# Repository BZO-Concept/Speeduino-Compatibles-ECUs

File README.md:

# Speeduino-Compatibles-ECUs
everything we need for run BZO ECUs

use .ini in ECUdef file in Tunerstudio, with the good firmware. 
Firmwares are uploaded with XLoader (https://github.com/binaryupdates/xLoader) for Arduino, and STM32Cube IDE for STM32

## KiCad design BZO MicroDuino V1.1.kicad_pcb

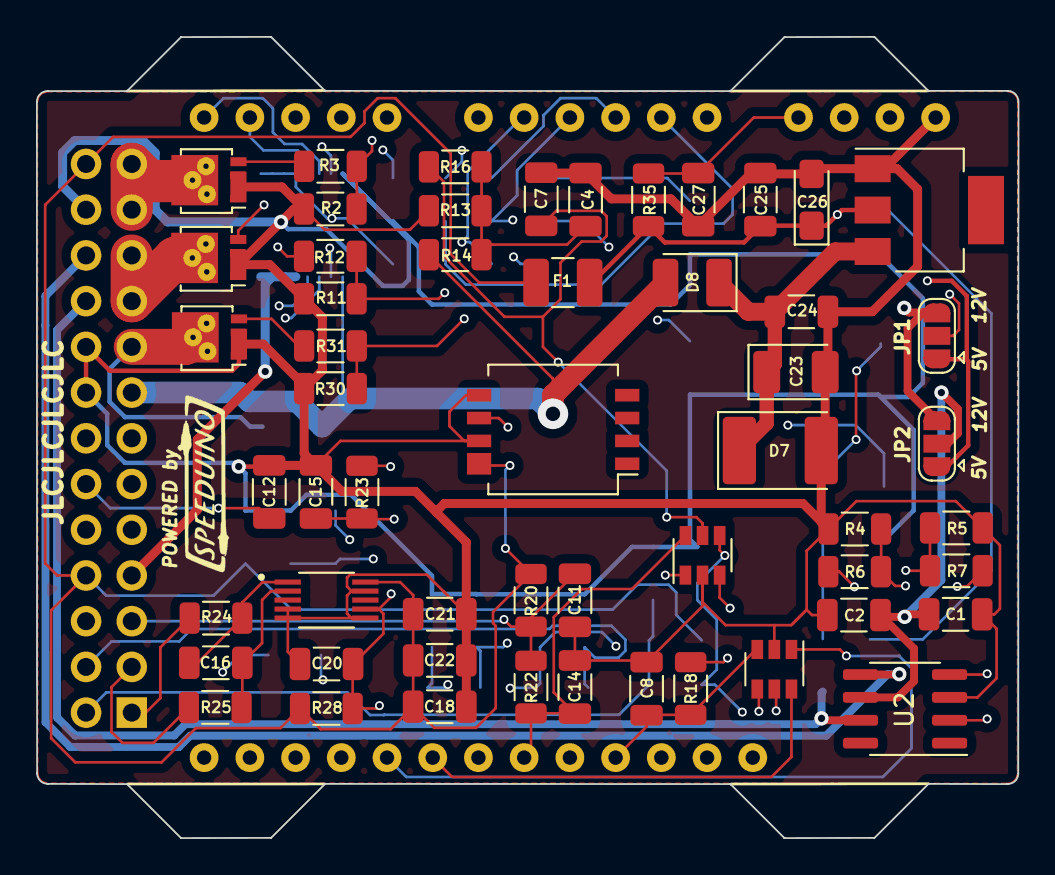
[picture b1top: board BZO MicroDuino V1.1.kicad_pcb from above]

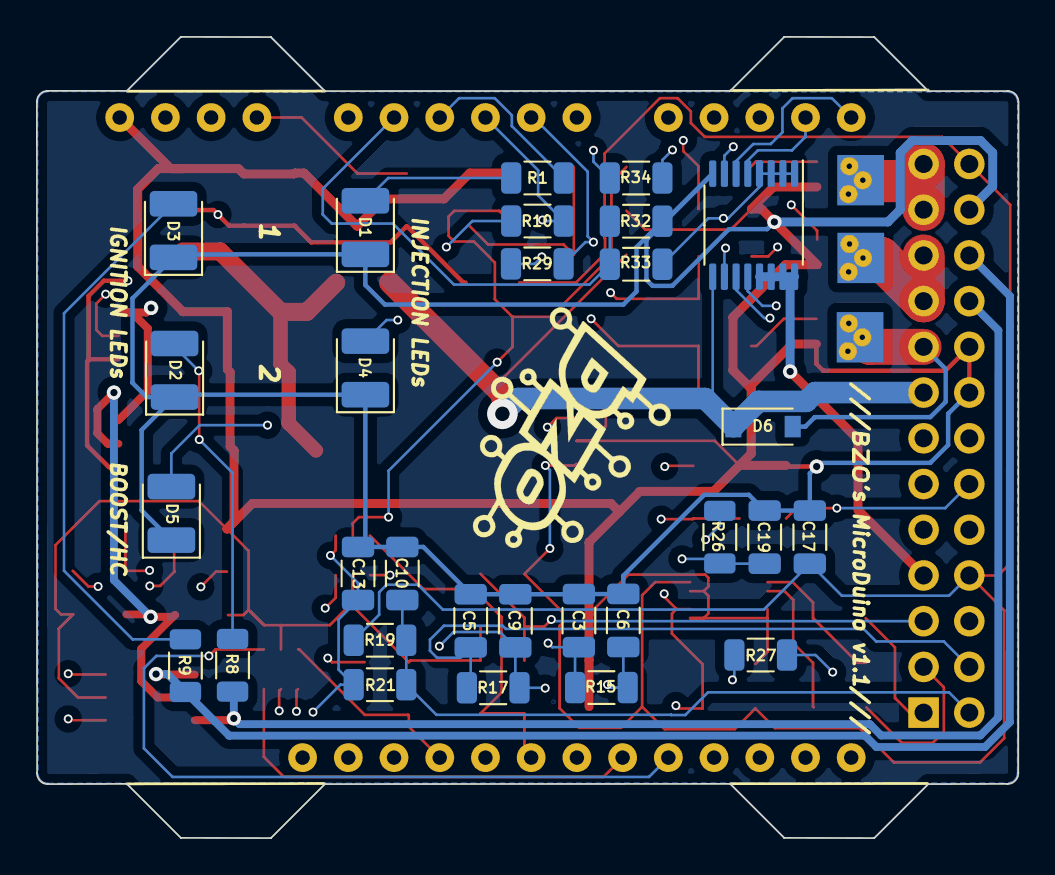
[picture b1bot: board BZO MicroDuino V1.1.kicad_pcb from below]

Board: 4 copper layers, 54.5 x 44.5 mm, 87 parts (30 on the bottom side), 60 nets.

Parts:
C1, C3, C4, C5, C10, C11, C12, C17, C19, C21, C24, C25: 0.1uF; C_1206_3216Metric
C2, C22: 1uF; C_1206_3216Metric
C6, C7, C9, C13, C14, C15: 0.22uF; C_1206_3216Metric
C8: 470pf; C_1206_3216Metric
C16: 0.001uF; C_1206_3216Metric
C18, C20: 0.01uF; C_1206_3216Metric
C23: 10uF; CP_EIA-3528-21_Kemet-B_Pad1.50x2.35mm_HandSolder
C26: 47uF; CP_EIA-3216-10_Kemet-I_Pad1.58x1.35mm_HandSolder
C27: 22uF; C_1206_3216Metric
D1, D2, D3, D4#2, D5: LED; LED_1210_3225Metric_Pad1.42x2.65mm_HandSolder
D4: LED; logo BZO
D6: 1N4448WQ-7-F; D_SOD-123
D7: D_TVS; D_2114_3652Metric_Pad1.85x3.75mm_HandSolder
D8: RB060MM-60TR; LED_1210_3225Metric_Pad1.42x2.65mm_HandSolder
F1: Polyfuse; Fuse_1210_3225Metric_Pad1.42x2.65mm_HandSolder
J1: Conn_02x13_Counter_Clockwise; PinHeader_2x13_P2.54mm_Horizontal
JP1, JP2: SolderJumper_3_Open; SolderJumper-3_P1.3mm_Open_RoundedPad1.0x1.5mm
Q1, Q2, Q3: Q_NMOS_GDS; LFPAK33_POWERPAD
R1, R10, R29: 150R; R_1206_3216Metric
R2, R4, R5, R11, R30, R32: 100k; R_1206_3216Metric
R3: 1k; SPEEDUINO PETIT
R3#2, R6, R7, R12, R13, R27, R28, R31, R33: 1k; R_1206_3216Metric
R8, R9: 2.4k; R_1206_3216Metric
R14: 3.9k; R_1206_3216Metric
R15, R16, R17, R18, R21, R22, R23: 470R; R_1206_3216Metric
R19, R20: 2.49k; R_1206_3216Metric
R24, R25, R26, R34: 10k; R_1206_3216Metric
R35: 120R; R_1206_3216Metric
U1: MEGA_PRO_EMBED_CH340G___ATMEGA2560; MODULE_MEGA_PRO_EMBED_CH340G___ATMEGA2560
U2: TC4424EPA/TC4424VPA/UCC27324DR; SOIC-8_3.9x4.9mm_P1.27mm
U3, U4: SP0505BAHTG; SOT-23-6
U5: MAX9924UAUB+
U6: KP212F1701
U7: ULN2003TTR; TSSOP-16_4.4x5mm_P0.65mm
U8: AMS1117-5.0; SOT-223

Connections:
5V-12V_TACHO: JP1.2, R34.2
+12V: D6.1, D8.2, J1.15, JP1.3, JP2.3, R14.2, U7.9
ADC-Clamp-1: C6.1, R15.1, U1.A2, U3.1
ADC-Clamp-2: C9.1, R17.1, U1.A8, U3.3
ADC-Clamp-3: C13.1, R21.1, U1.A0, U3.4
ADC-Clamp-4: C7.1, R16.1, U1.A4, U3.5
ADC-Clamp-5: C14.1, R22.1, U1.A10, U3.6
ADC-Clamp-6: R27.2, U1.D32, U4.1
ADC-Clamp-7: C15.1, R23.1, U1.A12, U4.5
ADC-Clamp-8: C20.2, R28.1, U1.D19, U4.4, U5.7
ADC-Clamp-9: C8.2, R18.1, U1.A6, U4.3
ADC-Clamp-10: C19.2, R26.1, U1.A14, U4.6
BOOST-OUT: D6.2, J1.17, Q3.5
CLT_Sensor: C11.1, J1.5, R20.1, R22.2
CTPS-ANALOG_in: C12.1, J1.12, R23.2
Clutch_in: J1.14, R27.1
FAN-OUT: J1.11, U7.11
FUELPUMP-OUT: J1.9, U7.12
GND: C1.1, C2.1, C3.2, C4.2, C5.2, C6.2, C7.2, C8.1, C9.2, C10.2, C11.2, C12.2, C13.2, C14.2, C15.2, C17.2, C18.2, C19.1, C20.1, C21.2, C22.2, C23.2, C24.2, C25.2, C26.2, C27.2, D1.1, D2.1, D3.1, D4#2.1, D5.1, D7.2, J1.16, J1.18, J1.24, Q1.1, Q1.2, Q1.3, Q2.1, Q2.2, Q2.3, Q3.1, Q3.2, Q3.3, R2.2, R4.2, R5.1, R11.2, R13.1, R30.2, R32.1, U1.GND_1, U2.3, U3.2, U4.2, U5.4, U5.5, U5.6, U5.9, U6.6, U6.8, U7.8, U8.1
IAT_Sensor: C10.1, J1.2, R19.1, R21.2
IDLE-OUT: J1.7, U7.13, U7.14, U7.15, U7.16
IGN-1-OUT: J1.22, R9.1, U2.5
IGN-2-OUT: J1.20, R8.1, U2.7
INJ-1-OUT: J1.23, J1.25, Q1.5
INJ-2-OUT: J1.19, J1.21, Q2.5
MAP-sensor: J1.6, R18.2
MCU-D5: R32.2, R33.1, U1.D5
MCU-D7: R1.2, R2.1, R3#2.2, U1.D7
MCU-D9: R10.2, R11.1, R12.2, U1.D9
MCU-D11: R29.2, R30.1, R31.2, U1.D11
MCU-D23: U1.D23, U7.5
MCU-D25: U1.D25, U7.6
MCU-D34: U1.D34, U7.7
MCU-D38: R4.1, R6.2, U1.D38
MCU-D40: R5.2, R7.2, U1.D40
unnamed: C4.1, R13.2, R14.1, R16.2
unnamed: C16.1, R24.1, U5.1
unnamed: C16.2, R25.1, U5.2
unnamed: D1.2, R1.1
unnamed: D2.2, R8.2
unnamed: D3.2, R9.2
unnamed: D4#2.2, R10.1
unnamed: D5.2, R29.1
unnamed: Q1.4, R3#2.1
unnamed: Q2.4, R12.1
unnamed: Q3.4, R31.1
unnamed: R6.1, U2.2
unnamed: R7.1, U2.4
unnamed: R26.2, U6.7
unnamed: R33.2, U7.1, U7.2, U7.3, U7.4
O2_Sensor: C5.1, J1.4, R17.2
RESET: C27.1, R35.1, U1.RST
TACHO-OUT: J1.13, R34.1, U7.10
TPS_Sensor: C3.1, J1.10, R15.2
VDD: C25.1, C26.1, F1.2, JP1.1, JP2.1, R35.2, U1.5V_1, U8.2
VDDA: C17.1, C18.1, C21.1, C22.1, F1.1, J1.8, J1.26, R19.2, R20.2, R28.2, U5.10, U6.5
VR1+: J1.1, R24.2
VR1-: J1.3, R25.2
VRegIn: C23.1, C24.1, D7.1, D8.1, U8.3
Vdrive: C1.2, C2.2, JP2.2, U2.6

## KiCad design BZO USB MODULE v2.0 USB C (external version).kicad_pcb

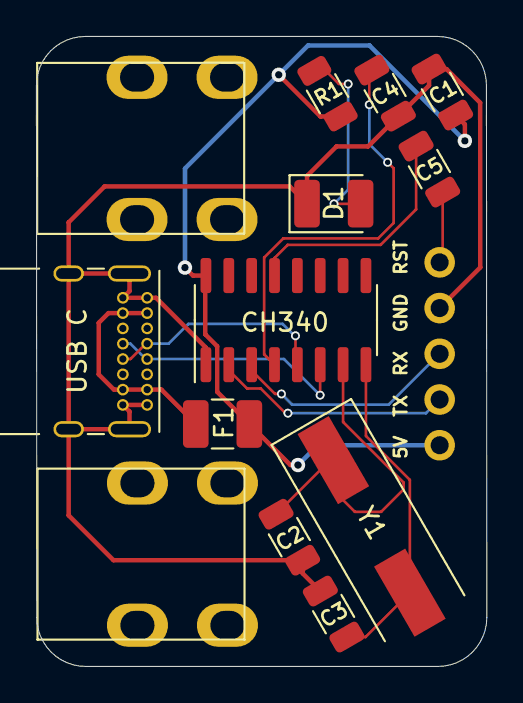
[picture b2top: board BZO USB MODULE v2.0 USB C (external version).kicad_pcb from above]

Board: 2 copper layers, 25.0 x 35.0 mm, 15 parts (1 on the bottom side), 13 nets.

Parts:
C1, C5#3: 0.1uF; C_1206_3216Metric
C2, C3: 22pF; C_1206_3216Metric
C4: 0.01uF; C_1206_3216Metric
C5, C5#2: 0.1uF; screw_terminal_M4_horizontal
CH340: CH340G; SOIC-16_3.9x9.9mm_P1.27mm
D1: LED; LED_1210_3225Metric_Pad1.42x2.65mm_HandSolder
F1: Polyfuse 500mA; Fuse_1210_3225Metric_Pad1.42x2.65mm_HandSolder
J2: Conn_sortie_module; PinHeader_1x05_P2.54mm_Vertical
R1: 150R; R_1206_3216Metric
USB C: USB_C_Receptacle; USB_C_Receptacle_GCT_USB4085
Y1: 12Mhz; logo BZO
Y1#2: 12Mhz; Crystal_SMD_HC49-SD

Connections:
+5V: C1.2, CH340.16, F1.1, J2.1, R1.2
GND: C1.1, C2.2, C3.2, C4.2, CH340.1, D1.1, J2.4, USB C.A1, USB C.A12, USB C.B1, USB C.B12, USB C.S1
unnamed: C2.1, CH340.7, Y1#2.1
unnamed: C3.1, CH340.8, Y1#2.2
unnamed: C4.1, CH340.4
unnamed: C5#3.2, CH340.13
unnamed: D1.2, R1.1
unnamed: F1.2, USB C.A4, USB C.A9, USB C.B4, USB C.B9
RD+: CH340.5, USB C.A6, USB C.B6
RD-: CH340.6, USB C.A7, USB C.B7
RESET: C5#3.1, J2.5
RX0_D0: CH340.2, J2.2
TX0_D1: CH340.3, J2.3

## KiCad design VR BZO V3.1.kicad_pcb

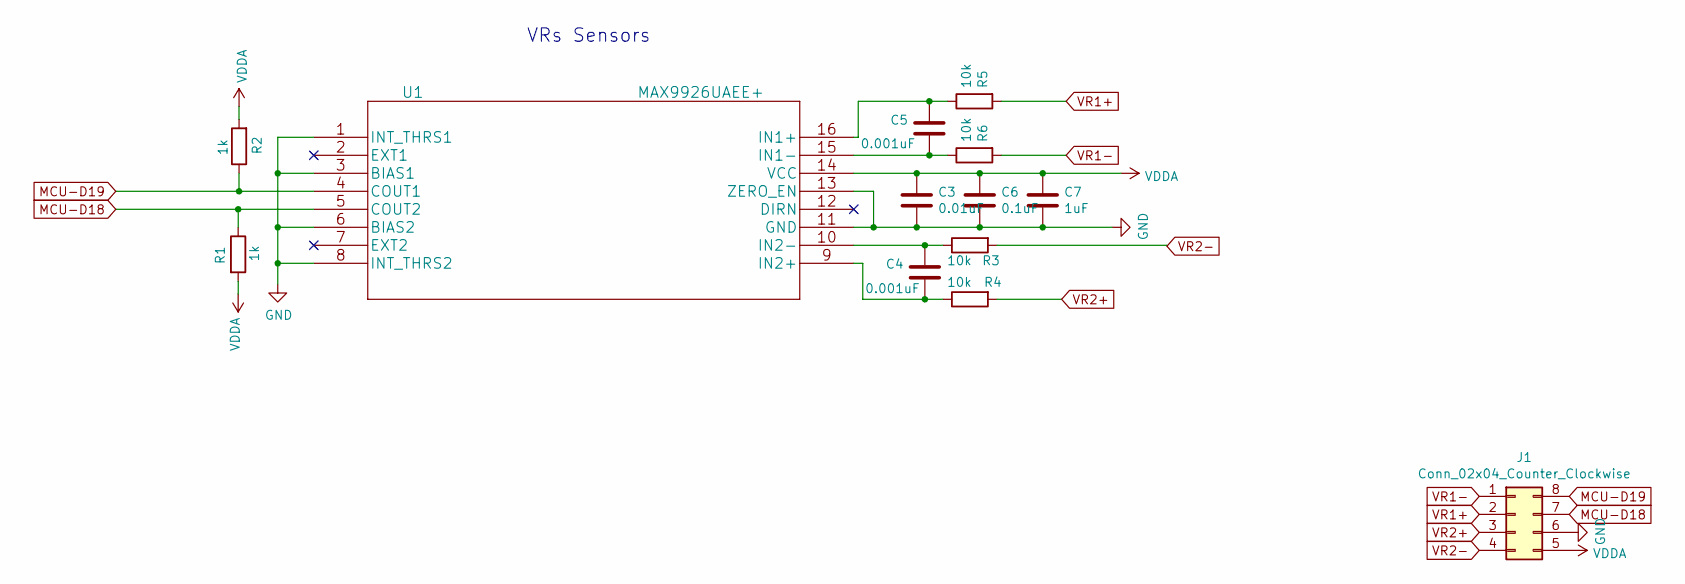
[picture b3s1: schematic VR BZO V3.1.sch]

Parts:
C3: 0.01uF; C_0805_2012Metric_Pad1.18x1.45mm_HandSolder; Manufacturer_Part_Number 12061C103KAT2A
C4, C5: 0.001uF; C_0805_2012Metric_Pad1.18x1.45mm_HandSolder; Manufacturer_Part_Number 1206SC102KAT1A
C6: 0.1uF; C_0805_2012Metric_Pad1.18x1.45mm_HandSolder; Manufacturer_Part_Number 12061C104KAT2A
C7: 1uF; C_0805_2012Metric_Pad1.18x1.45mm_HandSolder; Manufacturer_Part_Number 12063D105KAT2A
J1: Conn_02x04_Counter_Clockwise; DIP-8_W7.62mm_Socket
R1, R2: 1k; R_0805_2012Metric_Pad1.20x1.40mm_HandSolder; Manufacturer_Part_Number CR1206-FX-1001ELF
R3, R4, R5, R6: 10k; R_0805_2012Metric_Pad1.20x1.40mm_HandSolder; Manufacturer_Part_Number CR1206-FX-1002ELF
U1: MAX9926UAEE+; QSOP-16_3.9x4.9mm_P0.635mm; Manufacturer_Part_Number MAX9926UAEE+

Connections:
GND: C3.2, C6.2, C7.2, J1.6, U1.1 (INT_THRS1), U1.3 (BIAS1), U1.6 (BIAS2), U1.8 (INT_THRS2), U1.11 (GND), U1.13 (ZERO_EN)
MCU-D18: J1.7, R1.1, U1.5 (COUT2)
MCU-D19: J1.8, R2.1, U1.4 (COUT1)
unnamed: C4.1, R3.1, U1.10 (IN2-)
unnamed: C4.2, R4.1, U1.9 (IN2+)
unnamed: C5.1, R5.1, U1.16 (IN1+)
unnamed: C5.2, R6.1, U1.15 (IN1-)
VDDA: C3.1, C6.1, C7.1, J1.5, R1.2, R2.2, U1.14 (VCC)
VR1+: J1.2, R5.2
VR1-: J1.1, R6.2
VR2+: J1.3, R4.2
VR2-: J1.4, R3.2

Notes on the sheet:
VRs Sensors

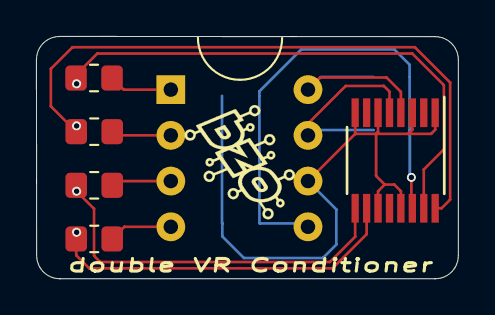
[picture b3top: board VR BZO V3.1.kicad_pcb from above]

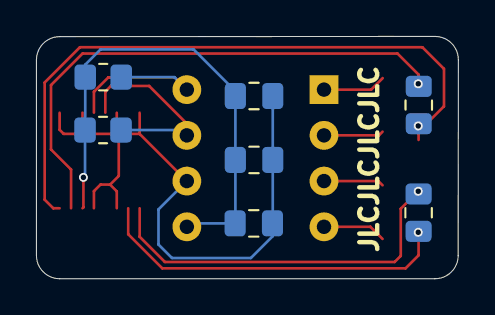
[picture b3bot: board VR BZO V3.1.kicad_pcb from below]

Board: 2 copper layers, 23.4 x 13.5 mm, 14 parts (7 on the bottom side), 12 nets.

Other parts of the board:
LOGO: LOGO; LOGO BZO petit

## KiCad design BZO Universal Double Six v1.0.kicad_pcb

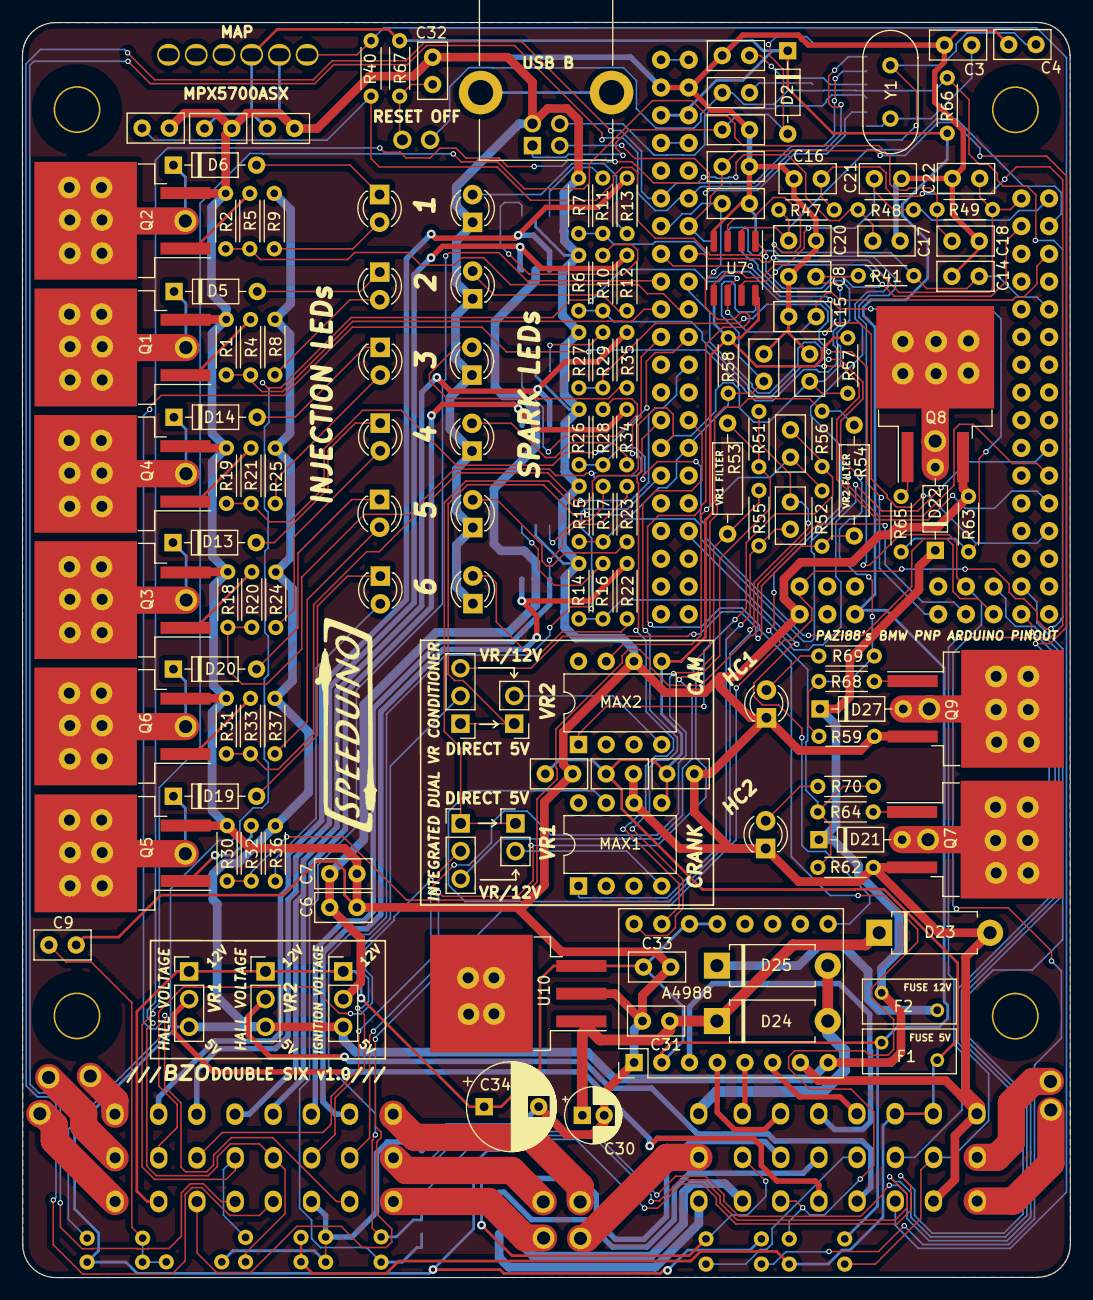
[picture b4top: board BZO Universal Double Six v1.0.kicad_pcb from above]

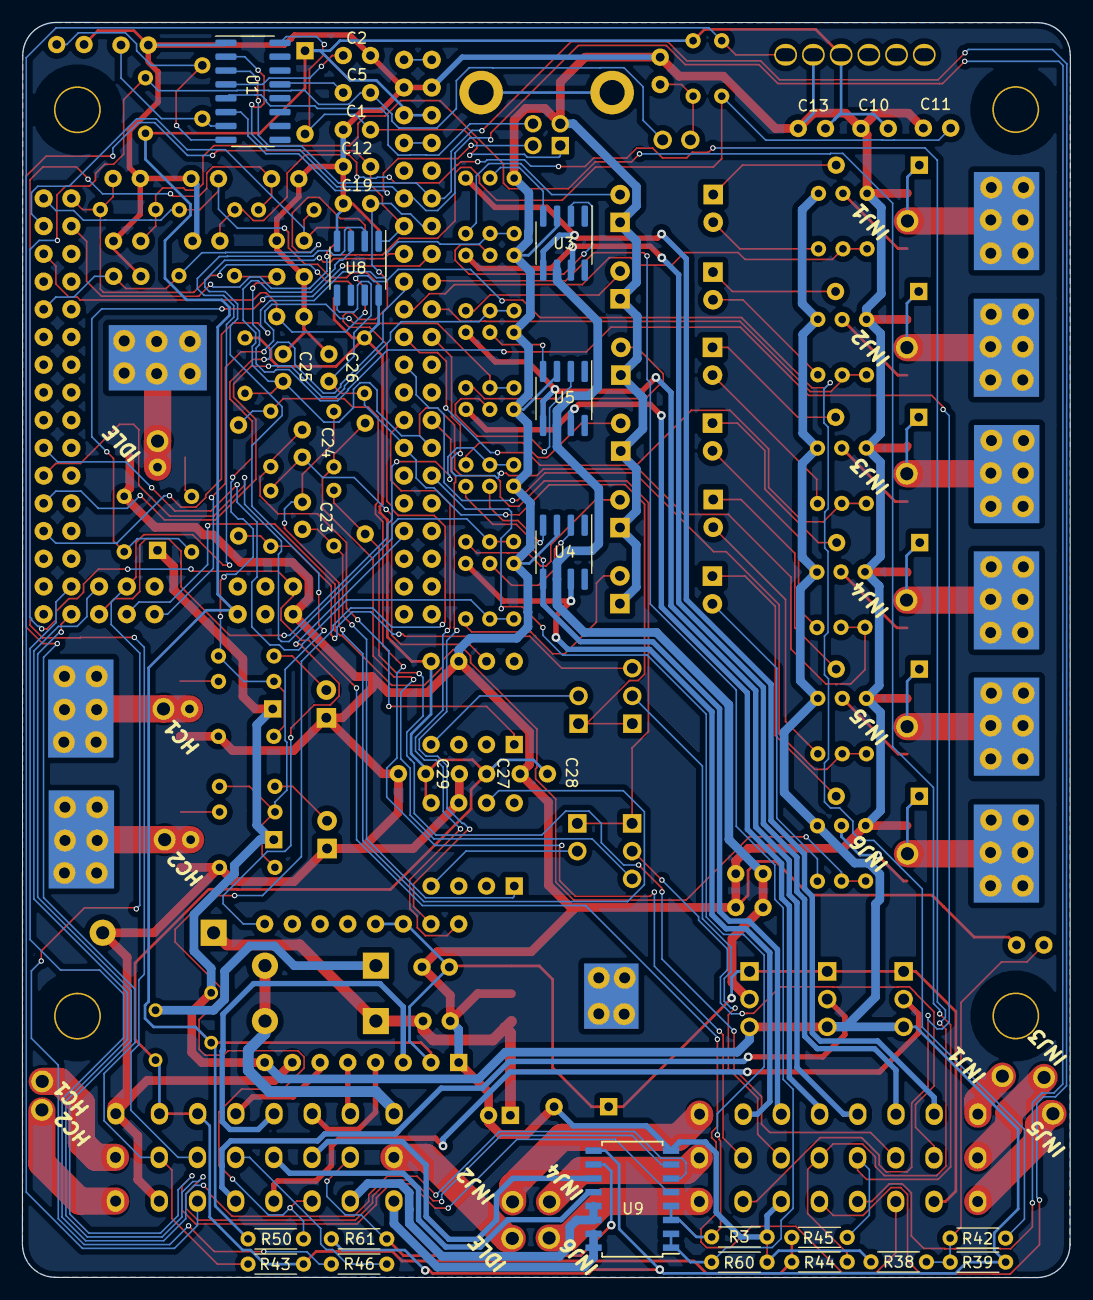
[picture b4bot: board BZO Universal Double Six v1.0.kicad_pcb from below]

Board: 2 copper layers, 96.0 x 115.0 mm, 185 parts (17 on the bottom side), 144 nets.

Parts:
A4988: Pololu_Breakout_A4988; Pololu_Breakout-16_15.2x20.3mm
C1, C5, C6, C8, C9, C16, C17, C18, C19, C28, C31, C33: 0.1uF; C_Disc_D5.0mm_W2.5mm_P2.50mm
C2, C10, C25, C26, C27: 0.01uF; C_Disc_D5.0mm_W2.5mm_P2.50mm
C3, C4: 22pF; C_Disc_D5.0mm_W2.5mm_P2.50mm
C7, C13, C29: 1uF; C_Disc_D5.0mm_W2.5mm_P2.50mm
C11: 470pf; C_Disc_D5.0mm_W2.5mm_P2.50mm
C12, C14, C15, C20, C21, C22: 0.22uF; C_Disc_D5.0mm_W2.5mm_P2.50mm
C23, C24: 0.001uF; C_Disc_D5.0mm_W2.5mm_P2.50mm
C30: 10uF; CP_Radial_D5.0mm_P2.00mm
C32: 22uF; C_Disc_D5.0mm_W2.5mm_P2.50mm
C34: 47uF; CP_Radial_D8.0mm_P5.00mm
D2, D5, D6, D13, D14, D19, D20, D21, D22, D27: 1N914TAP; D_DO-35_SOD27_P7.62mm_Horizontal
D3, D4, D7, D8, D9, D10, D11, D12, D15, D16, D17, D18, D26, D28: LED; LED_D3.0mm
D23: D_TVS; D_DO-15_P10.16mm_Horizontal
D24, D25: SB230TA; D_DO-15_P10.16mm_Horizontal
F1: Polyfuse; Fuse_BelFuse_0ZRE0005FF_L8.3mm_W3.8mm
F2: Polyfuse 2; Fuse_BelFuse_0ZRE0005FF_L8.3mm_W3.8mm
J1: USB_B; USB_B_Lumberg_2411_02_Horizontal
J2: connecteur ECU 1; CONNECTOR_ECU_3X8PINS_GENERIC
J3: connecteur ECU 2; CONNECTOR_ECU_3X8PINS_GENERIC
J4, J5, J6, J7, J8, J9, J10, J11, J12, J13, J14, J15, J16, J17, J18, J19, J20, J21: Conn_01x01_Female; WIRE_CONNECTOR
JP1: SWITCH VR HALL 1; PinHeader_1x03_P2.54mm_Vertical
JP2: SWITCH VR HALL 2; PinHeader_1x03_P2.54mm_Vertical
JP3: MAX OUT 1; PinHeader_1x02_P2.54mm_Vertical
JP4: MAX OUT 2; PinHeader_1x02_P2.54mm_Vertical
JP5: VR1 Voltage; PinHeader_1x03_P2.54mm_Vertical
JP6: Ignition Voltage; PinHeader_1x03_P2.54mm_Vertical
JP7: VR2 Voltage; PinHeader_1x03_P2.54mm_Vertical
JP8: Jumper_NO_Small; PinHeader_1x02_P2.54mm_Vertical
MAX1: MAX VR1; DIP-8_W7.62mm
MAX2: MAX VR2; DIP-8_W7.62mm
Q1, Q2, Q3, Q4, Q5, Q6, Q7, Q8, Q9: Q_NMOS_GDS; TO-263-2_COOLING_PAD
R1, R2, R3, R6, R7, R14, R15, R18, R19, R26, R27, R30, R31, R59, R60, R62, R63: 100k; R_Axial_DIN0204_L3.6mm_D1.6mm_P5.08mm_Horizontal
R4, R5, R10, R11, R16, R17, R20, R21, R28, R29, R32, R33, R38, R46, R50, R57, R58, R64, R65, R68: 1k; R_Axial_DIN0204_L3.6mm_D1.6mm_P5.08mm_Horizontal
R8, R9, R12, R13, R22, R23, R24, R25, R34, R35, R36, R37, R43: 2.4k; R_Axial_DIN0204_L3.6mm_D1.6mm_P5.08mm_Horizontal
R39: 3.9k; R_Axial_DIN0204_L3.6mm_D1.6mm_P5.08mm_Horizontal
R40, R41, R42, R47, R48, R49: 470R; R_Axial_DIN0204_L3.6mm_D1.6mm_P5.08mm_Horizontal
R44, R45: 2.49k; R_Axial_DIN0204_L3.6mm_D1.6mm_P5.08mm_Horizontal
R51, R52, R55, R56, R61, R66: 10k; R_Axial_DIN0204_L3.6mm_D1.6mm_P5.08mm_Horizontal
R53, R54: 4.7K 2W; R_Axial_DIN0207_L6.3mm_D2.5mm_P10.16mm_Horizontal
R67: 120R; R_Axial_DIN0204_L3.6mm_D1.6mm_P5.08mm_Horizontal
R69, R70: 100R/150R; R_Axial_DIN0204_L3.6mm_D1.6mm_P5.08mm_Horizontal
U1: CH340G; SOIC-16_3.9x9.9mm_P1.27mm
U2: MEGA_PRO_EMBED_CH340G___ATMEGA2560; MODULE_MEGA_PRO_EMBED_CH340G___ATMEGA2560
U3, U4, U5: TC4424EPA/TC4424VPA/UCC27324DR; SOIC-8_3.9x4.9mm_P1.27mm
U6: MPX4250AP/MPX5700ASX; PinHeader_1x06_P2.54mm_Vertical
U7, U8: SP721ABG/SP721ABTG; SOIC-8_3.9x4.9mm_P1.27mm
U9: ULN2003A; SOIC-16W_5.3x10.2mm_P1.27mm
U10: LM2940T-5.0/LF08; TO-263-3_TabPin4_COOLING_PAD
Y1: 12Mhz; Crystal_HC49-U_Vertical

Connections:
12V-SW: D24.2, D25.2, J2.1
+5VA: C27.1, C28.1, C29.1, F1.1, J2.6, J2.7, MAX1.5, MAX2.5, R43.1, R44.2, R45.2, R57.2, R58.2, U7.8, U8.8
+5V_CH340: C1.2, D2.2, J1.1, U1.16
+5V_COM_EXT: A4988.2, A4988.13, A4988.14, C10.1, C13.1, C33.1, C34.1, D2.1, F1.2, J3.18, JP5.1, JP6.1, JP7.1, R50.2, R66.2, R67.2, U2.5V_1, U2.5V_2, U2.5V_3, U6.3, U10.3
+12V: A4988.8, D21.1, D22.1, D27.1, F2.2, JP5.3, JP6.3, JP7.3, R8.2, R9.2, R24.2, R25.2, R36.2, R37.2, R39.2, R61.2, U9.9
ADC-Clamp-1: C11.2, R40.1, U2.A3, U7.1
ADC-Clamp-2: C20.1, R47.1, U2.A2, U7.2
ADC-Clamp-3: C14.1, R41.1, U2.A8, U7.3
ADC-Clamp-4: C21.1, R48.1, U2.A0, U7.5
ADC-Clamp-5: C15.1, R42.1, U2.A4, U7.6
ADC-Clamp-6: C22.1, R49.1, U2.A1, U7.7
ADC-Clamp-7: C12.1, J2.15, R43.2, U2.D2, U8.1
ADC-Clamp-8: R46.2, U2.D51, U8.2
ADC-Clamp-9: C25.1, JP1.1, JP3.1, R57.1, U2.D19, U8.3
ADC-Clamp-10: C26.1, JP2.1, JP4.1, R58.1, U2.D18, U8.5
ALIM_VR1: J2.20, JP5.2
ALIM_VR2: J2.21, JP7.2
BOOST-OUT: J2.17, U9.15, U9.16
CLT_Sensor: C18.1, J3.12, R45.1, R49.2
CUSTOM1-OUT: J2.18, U9.13, U9.14
Clutch_in: J2.13, R46.1
FAN-OUT: J2.12, U9.12
FUELPUMP-OUT: J2.11, U9.11
GND_COM_EXT: A4988.1, A4988.7, C1.1, C2.2, C3.2, C4.2, C6.1, C7.1, C8.2, C9.2, C10.2, C11.1, C12.2, C13.2, C14.2, C15.2, C16.2, C17.2, C18.2, C19.1, C20.2, C21.2, C22.2, C25.2, C26.2, C27.2, C28.2, C29.2, C30.2, C31.2, C32.2, C33.2, C34.2, D7.1, D8.1, D9.1, D10.1, D15.1, D16.1, D23.2, D26.1, D28.1, J1.4, J2.8, J2.23, J3.22, MAX1.6, MAX2.6, Q1.3, Q2.3, Q3.3, Q4.3, Q5.3, Q6.3, Q7.3, Q8.3, Q9.3, R1.2, R2.2, R3.1, R6.2, R7.1, R14.2, R15.1, R18.1, R19.1, R26.2, R27.1, R30.1, R31.1, R38.1, R59.1, R60.1, R62.1, R63.1, U1.1, U2.GND_1, U2.GND_2, U2.GND_3, U3.3, U4.3, U5.3, U6.2, U7.4, U8.4, U9.8, U10.2
HC-1-OUT: J2.16, J5.1
HC-2-OUT: J2.24, J21.1
IAT_Sensor: C17.1, J3.13, R44.1, R48.2
IDLE-OUT: J2.9, J19.1
IGN-1-OUT: J3.2, R13.1, U3.5
IGN-2-OUT: J3.3, R12.1, U3.7
IGN-3-OUT: J3.4, R35.1, U5.5
IGN-4-OUT: J3.5, R34.1, U5.7
IGN-5-OUT: J3.6, R23.1, U4.5
IGN-6-OUT: J3.7, R22.1, U4.7
INJ-1-OUT: J3.1, J7.1
INJ-2-OUT: J3.8, J6.1
INJ-3-OUT: J3.9, J10.1
INJ-4-OUT: J3.16, J11.1
INJ-5-OUT: J3.17, J15.1
INJ-6-OUT: J3.24, J14.1
MAP_EXT: J2.22, R40.2, U6.1
MCU-D0: J3.20, U1.2, U2.RX
MCU-D1: J3.21, U1.3, U2.TX
MCU-D3: C19.2, J2.19, R50.1, U2.D3
MCU-D4: R62.2, R64.1, R70.2, U2.D4
MCU-D5: R63.2, R65.1, U2.D5
MCU-D6: R59.2, R68.1, R69.2, U2.D6
MCU-D7: R60.2, U2.D7, U9.1, U9.2
MCU-D8: R2.1, R5.2, U2.D8
MCU-D9: R1.1, R4.2, U2.D9
MCU-D10: R19.2, R21.2, U2.D10
MCU-D11: R18.2, R20.2, U2.D11
MCU-D12: R31.2, R33.2, U2.D12
MCU-D16: A4988.16, U2.D16
MCU-D17: A4988.15, U2.D17
MCU-D21: R3.2, U2.D21, U9.3, U9.4
MCU-D24: A4988.9, U2.D24
MCU-D34: R14.1, R16.2, U2.D34
MCU-D36: R15.2, R17.2, U2.D36
MCU-D38: R6.1, R10.2, U2.D38
MCU-D40: R7.2, R11.2, U2.D40
MCU-D45: U2.D45, U9.6
MCU-D47: U2.D47, U9.5
MCU-D48: R26.1, R28.2, U2.D48
MCU-D49: U2.D49, U9.7
MCU-D50: R30.2, R32.2, U2.D50
MCU-D52: R27.2, R29.2, U2.D52
unnamed: C2.1, U1.4
unnamed: C3.1, U1.7, Y1.1
unnamed: C4.1, U1.8, Y1.2
unnamed: C5.2, U1.13
unnamed: C9.1, R38.2, R39.1, R42.2
unnamed: C23.1, MAX1.7, R51.1
unnamed: C23.2, MAX1.1, R55.1
unnamed: C24.1, MAX2.7, R52.1
unnamed: C24.2, MAX2.1, R56.1
unnamed: C32.1, JP8.1, R67.1
unnamed: D3.1, D5.2
unnamed: D3.2, R8.1
unnamed: D4.1, D6.2
unnamed: D4.2, R9.1
unnamed: D5.1, J8.1, Q1.2
unnamed: D6.1, J9.1, Q2.2
unnamed: D7.2, R12.2
unnamed: D8.2, R13.2
unnamed: D9.2, R22.2
unnamed: D10.2, R23.2
unnamed: D11.1, D13.2
unnamed: D11.2, R24.1
unnamed: D12.1, D14.2
unnamed: D12.2, R25.1
unnamed: D13.1, J12.1, Q3.2
unnamed: D14.1, J13.1, Q4.2
unnamed: D15.2, R34.2
unnamed: D16.2, R35.2
unnamed: D17.1, D19.2
unnamed: D17.2, R36.1
unnamed: D18.1, D20.2
unnamed: D18.2, R37.1
unnamed: D19.1, J16.1, Q5.2
unnamed: D20.1, J17.1, Q6.2
unnamed: D21.2, J20.1, Q7.2
unnamed: D22.2, J18.1, Q8.2
unnamed: D25.1, F2.1
unnamed: D26.2, R69.1
unnamed: D27.2, J4.1, Q9.2
unnamed: D28.2, R70.1
unnamed: JP1.3, R51.2, R53.1
unnamed: JP2.3, R52.2, R54.1
unnamed: JP3.2, MAX1.4
unnamed: JP4.2, MAX2.4
unnamed: Q1.1, R4.1
unnamed: Q2.1, R5.1
unnamed: Q3.1, R20.1
unnamed: Q4.1, R21.1
unnamed: Q5.1, R32.1
unnamed: Q6.1, R33.1
unnamed: Q7.1, R64.2
unnamed: Q8.1, R65.2
unnamed: Q9.1, R68.2
unnamed: R10.1, U3.2
unnamed: R11.1, U3.4
unnamed: R16.1, U4.2
unnamed: R17.1, U4.4
unnamed: R28.1, U5.2
unnamed: R29.1, U5.4
unnamed: U2.3V3_1, U2.3V3_2
unnamed: U2.VIN_1, U2.VIN_2
O2_Sensor: C8.1, J3.23, R41.2
RD+: J1.3, U1.5
RD-: J1.2, U1.6
RESET: C5.1, J3.19, JP8.2, R66.1, U2.RESET
STEP-1A: A4988.4, J2.3
STEP-1B: A4988.3, J2.4
STEP-2A: A4988.5, J2.2
STEP-2B: A4988.6, J2.5
TACHO-OUT: J2.10, R61.1, U9.10
TPS_Sensor: C16.1, J2.14, R47.2
VR1+: J3.10, JP1.2
VR1-: J3.11, R53.2, R55.2
VR2+: J3.14, JP2.2
VR2-: J3.15, R54.2, R56.2
VRegIn: C30.1, C31.1, D23.1, D24.1, U10.1
Vdrive: C6.2, C7.2, JP6.2, U3.6, U4.6, U5.6

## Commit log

2024-06-14 Add files via upload
    caution. the internal baro is reversed in this version. see the datasheet of KP212
